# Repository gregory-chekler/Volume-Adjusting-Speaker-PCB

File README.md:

The circuit takes in a signal from an audio jack, that is of a frequency from about 40 Hz to 22 kHz (the range of human hearing). The LM 378 is supplied with 9 volts and the gain is at most 200 times. There is a 10k potentiometer which can modify the gain in a range such that there is no output sound to the point where the sound is 200 times the initial amplitude of the signal.
We chose the values shown below as specified in the LM378 datasheet in order to get a maximum of 200 times gain. We chose a potentiometer to regulate how much of the audio signal we want to pass through. The output is governed by this equation: Vout  = 200*(10k - R) * Vin
The variable resistance was connected to the inverting input so the amount of voltage to the terminal could be changed.

### LTSPice Circuit

Input to speaker:

Output From Amplifier:

Voltage Across Speaker:

### KiCad

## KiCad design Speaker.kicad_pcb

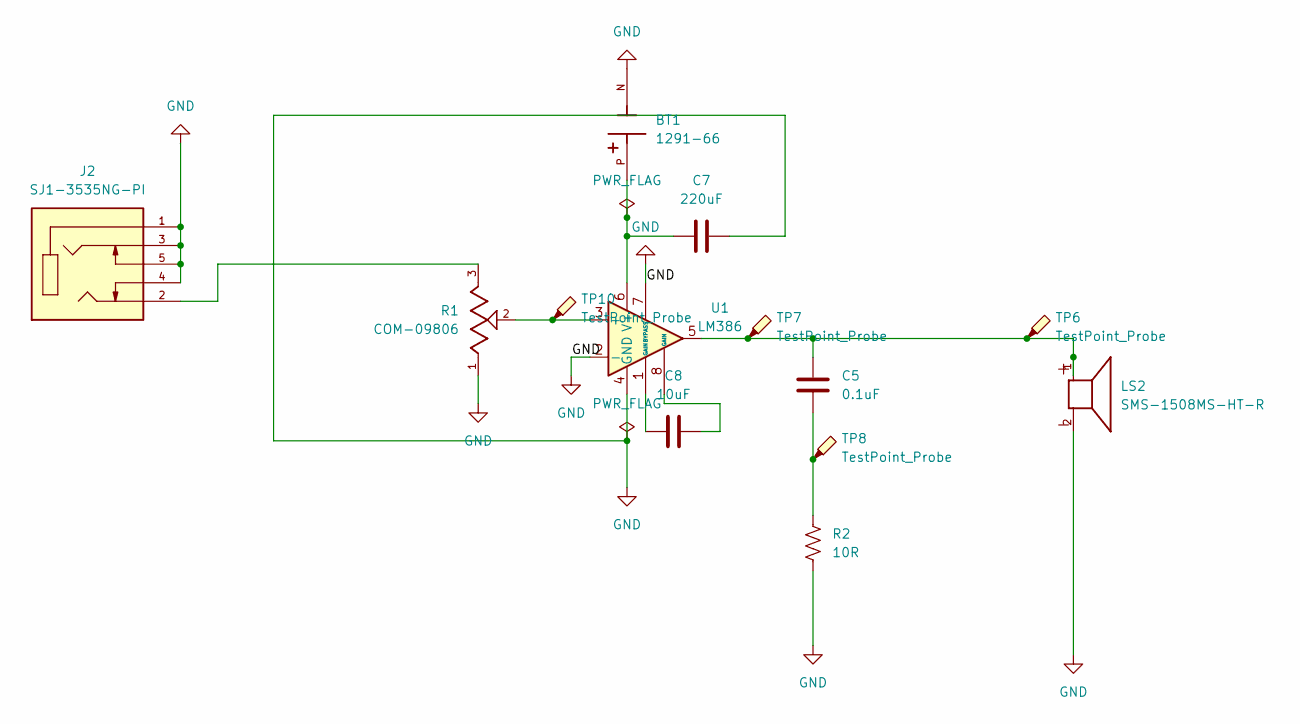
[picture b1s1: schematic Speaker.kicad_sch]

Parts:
BT1: 1291-66; BAT_1291-66; PARTREV A
C5: 0.1uF; CP_Radial_D6.3mm_P2.50mm
C7: 220uF; CP_Radial_D6.3mm_P2.50mm
C8: 10uF; CP_Radial_D6.3mm_P2.50mm
J2: SJ1-3535NG-PI; CUI_SJ1-3535NG-PI; PARTREV 1.02
LS2: SMS-1508MS-HT-R; SPKR_SMS-1508MS-HT-R; PARTREV 3/6/2020
R1: COM-09806; TRIM_COM-09806; PARTREV N/A
R2: 10R; R_Axial_DIN0207_L6.3mm_D2.5mm_P10.16mm_Horizontal
TP6, TP7, TP8, TP10: TestPoint_Probe; TestPoint_THTPad_3.0x3.0mm_Drill1.5mm
U1: LM386; DIP794W45P254L959H508Q8

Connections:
GND: BT1.N, C7.2, J2.1, J2.3, J2.4, J2.5, LS2.2, R1.1, R2.2, U1.2 (-), U1.4 (GND), U1.7 (BYPASS)
unnamed: C5.1, LS2.1, TP6.1, TP7.1, U1.5
unnamed: C5.2, R2.1, TP8.1
unnamed: C8.1, U1.8 (GAIN)
unnamed: C8.2, U1.1 (GAIN)
unnamed: J2.2, R1.3
unnamed: R1.2, TP10.1, U1.3 (+)
unnamed: BT1.P, C7.1, U1.6 (V+)

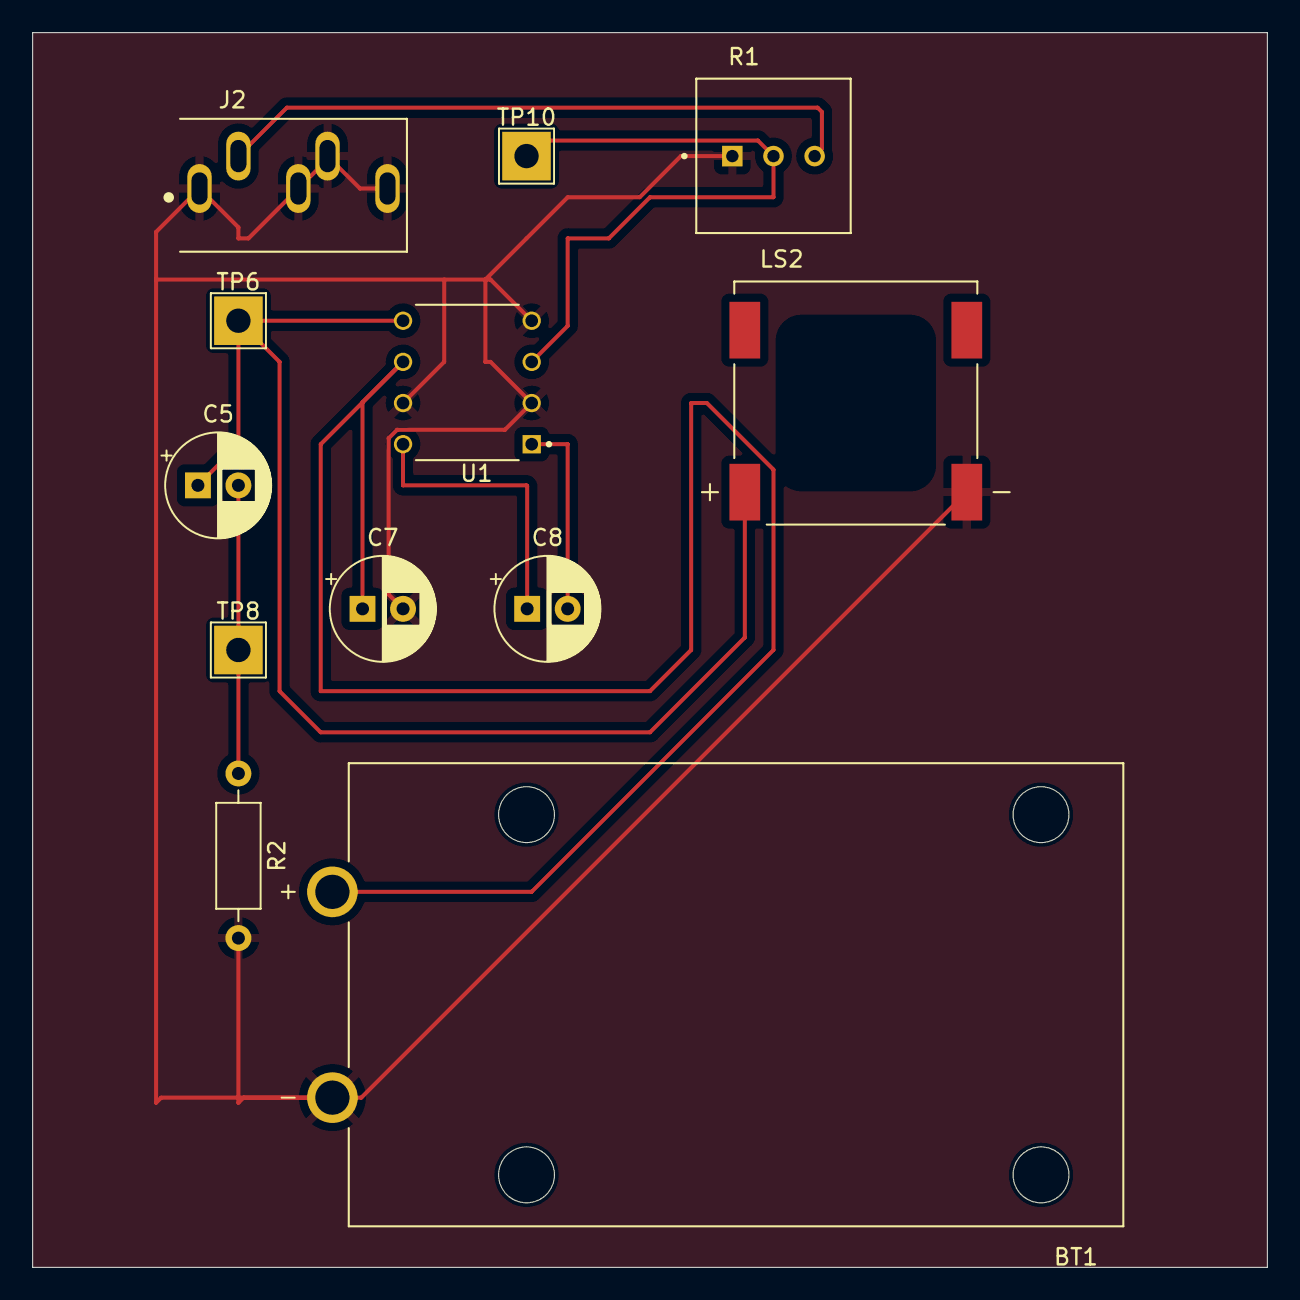
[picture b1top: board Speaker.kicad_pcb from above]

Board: 2 copper layers, 76.2 x 76.2 mm, 12 parts (0 on the bottom side), 8 nets.
